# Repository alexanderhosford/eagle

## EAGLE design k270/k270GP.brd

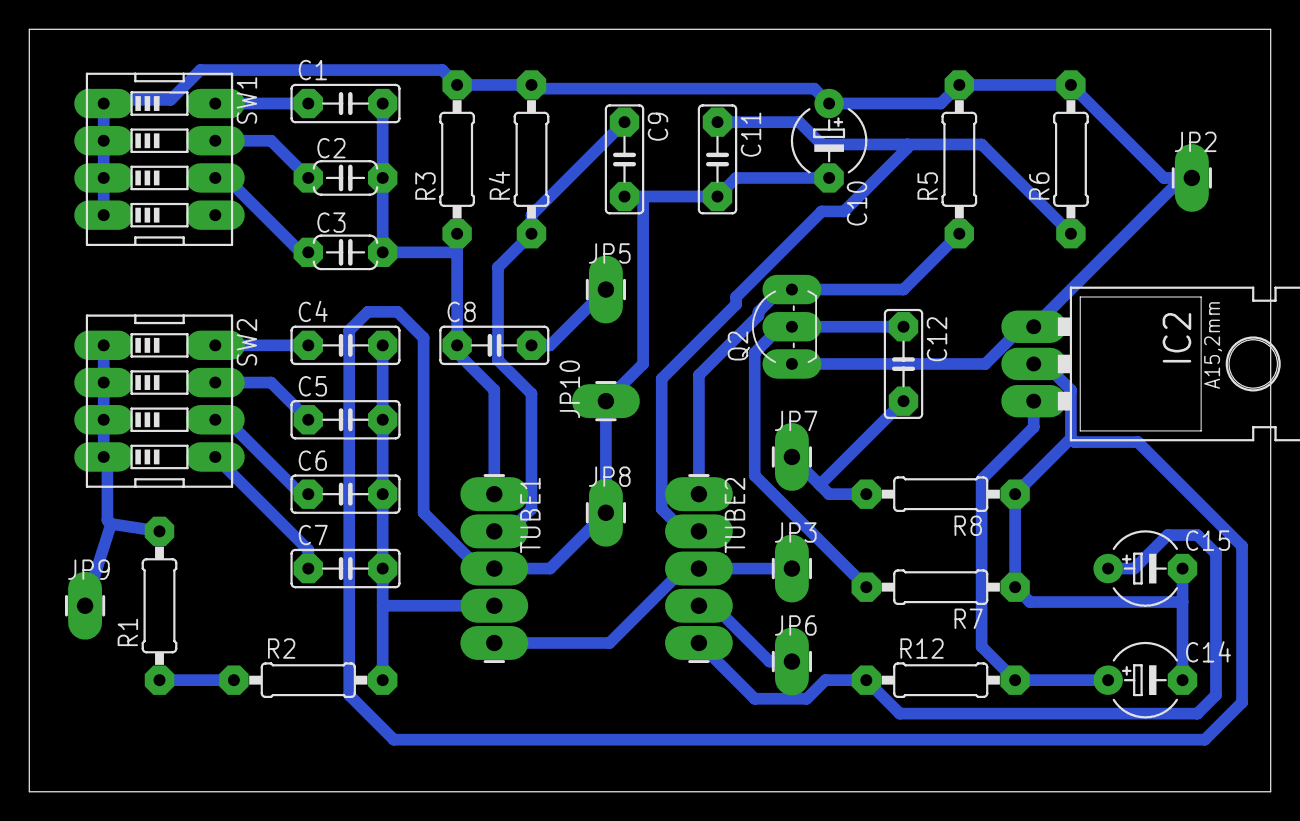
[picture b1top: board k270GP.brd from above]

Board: 2 copper layers, 84.8 x 52.1 mm, 37 parts (0 on the bottom side), 23 nets.

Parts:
C1, C6: 3n3; C050-025X075
C2: 820p; C050-024X044
C3: 330p; C050-024X044
C4: 100nF; C050-025X075
C5, C8: 10nF; C050-025X075
C7: 1n2; C050-025X075
C9, C11, C12: 0.1; C050-025X075
C10, C14, C15: 10µF; E5-5
IC2: 78XXL
JP2: +9V; 1X01_LONGPAD
JP3: pot1; 1X01_LONGPAD
JP5: pot3; 1X01_LONGPAD
JP6: potWiper; 1X01_LONGPAD
JP7: OUT.SIG; 1X01_LONGPAD
JP8: OUT.GND; 1X01_LONGPAD
JP9: IN.SIG; 1X01_LONGPAD
JP10: IN.GND; 1X01_LONGPAD
Q2: BSN254A; TO92-
R1, R8: 1M; 0207/10
R2: 47k; 0207/10
R3: 100k; 0207/10
R4, R6: 270k; 0207/10
R5: 180k; 0207/10
R7: 6k8; 0207/10
R12: 270R; 0207/10
SW1: LPF; EDG-04
SW2: HPF; EDG-04
TUBE1, TUBE2: JAN6841; 1X05_LONGPADS

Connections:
5V: C14.+, IC2.OUT, R12.2
9V: C10.+, IC2.IN, JP2.1, Q2.3, R3.2, R4.2, R5.2, R6.2, SW1.1, SW1.2, SW1.3, SW1.4
GND: C9.2, C10.-, C11.2, C14.-, C15.-, IC2.GND, JP8.1, JP10.1, R7.1, R8.1, TUBE1.3
unnamed: C1.1, SW1.8
unnamed: C2.1, SW1.7
unnamed: C3.1, SW1.6
unnamed: C1.2, C2.2, C3.2, C8.1, R3.1, TUBE1.1
unnamed: C4.1, SW2.8
unnamed: C5.1, SW2.7
unnamed: C6.1, SW2.6
unnamed: C7.1, SW2.5
unnamed: C4.2, C5.2, C6.2, C7.2, R2.2, TUBE1.4
unnamed: JP9.1, R1.2, SW2.1, SW2.2, SW2.3, SW2.4
unnamed: R1.1, R2.1
unnamed: C8.2, JP5.1
unnamed: C9.1, R4.1, TUBE1.2
unnamed: JP6.1, TUBE2.4
unnamed: C11.1, R6.1, TUBE2.2
unnamed: JP3.1, TUBE1.5, TUBE2.3
unnamed: C15.+, R12.1, TUBE2.5
unnamed: Q2.1, R5.1, TUBE2.1
unnamed: C12.1, Q2.2, R7.2
unnamed: C12.2, JP7.1, R8.2

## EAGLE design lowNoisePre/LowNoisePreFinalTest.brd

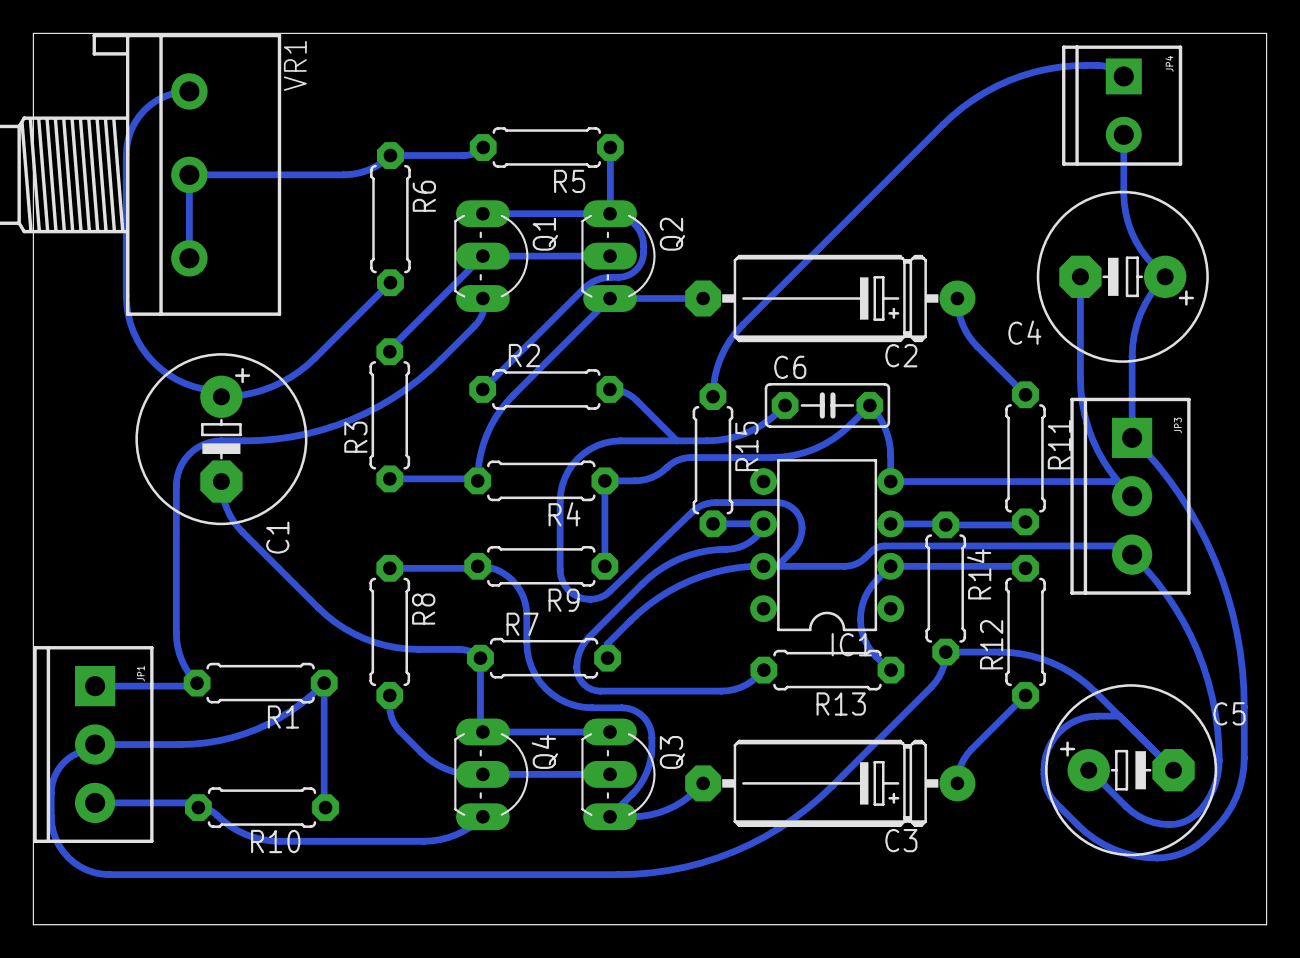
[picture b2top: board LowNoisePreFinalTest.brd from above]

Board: 2 copper layers, 73.9 x 53.4 mm, 30 parts (0 on the bottom side), 19 nets.

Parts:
C1: 1000µF; E5-10,5
C2, C3: 10µF; E15-5
C4, C5: 220µF; E5-10,5
C6: 100nF; C050-025X075
IC1: TL071P; DIL08
JP1: INPUT; SCREWTERMINAL-3.5MM-3
JP3: POWER; SCREWTERMINAL-3.5MM-3
JP4: OUTPUT; SCREWTERMINAL-3.5MM-2
Q1, Q4: 2N4403; TO92-BCE
Q2, Q3: BC549B; TO92-EBC
R1, R10: 3k3; 0207/7
R2, R7: 4k7; 0207/7
R3, R8: 680r; 0207/7
R4, R9: 2k2; 0207/7
R5: 22r; 0207/7
R6, R13, R14: 100k; 0207/7
R11, R12: 22k; 0207/7
R15: 100r; 0207/7
VR1: 10k; 3RP/1610N

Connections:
GND: C4.+, C5.-, JP1.2, JP3.1, JP4.2, R1.1, R10.1, R14.2
unnamed: C5.+, C6.1, IC1.7, JP3.3, R2.2, R7.2
unnamed: C4.-, C6.2, IC1.4, JP3.2, R4.1, R9.1
unnamed: JP4.1, R15.1
unnamed: IC1.6, R13.2, R15.2
unnamed: IC1.2, R12.2, R13.1
unnamed: IC1.3, R11.2, R14.1
unnamed: C3.+, R12.1
unnamed: C2.+, R11.1
unnamed: C3.-, Q3.E, R8.1, R9.2
unnamed: Q1.C, Q2.B, R3.2
unnamed: C2.-, Q2.E, R3.1, R4.2
unnamed: Q3.B, Q4.C, R8.2
unnamed: JP1.3, Q4.B, R10.2
unnamed: JP1.1, Q1.B, R1.2
unnamed: Q1.E, Q2.C, R2.1, R5.1
unnamed: C1.-, Q3.C, Q4.E, R7.1
unnamed: R5.2, R6.1, VR1.2, VR1.3
unnamed: C1.+, R6.2, VR1.1

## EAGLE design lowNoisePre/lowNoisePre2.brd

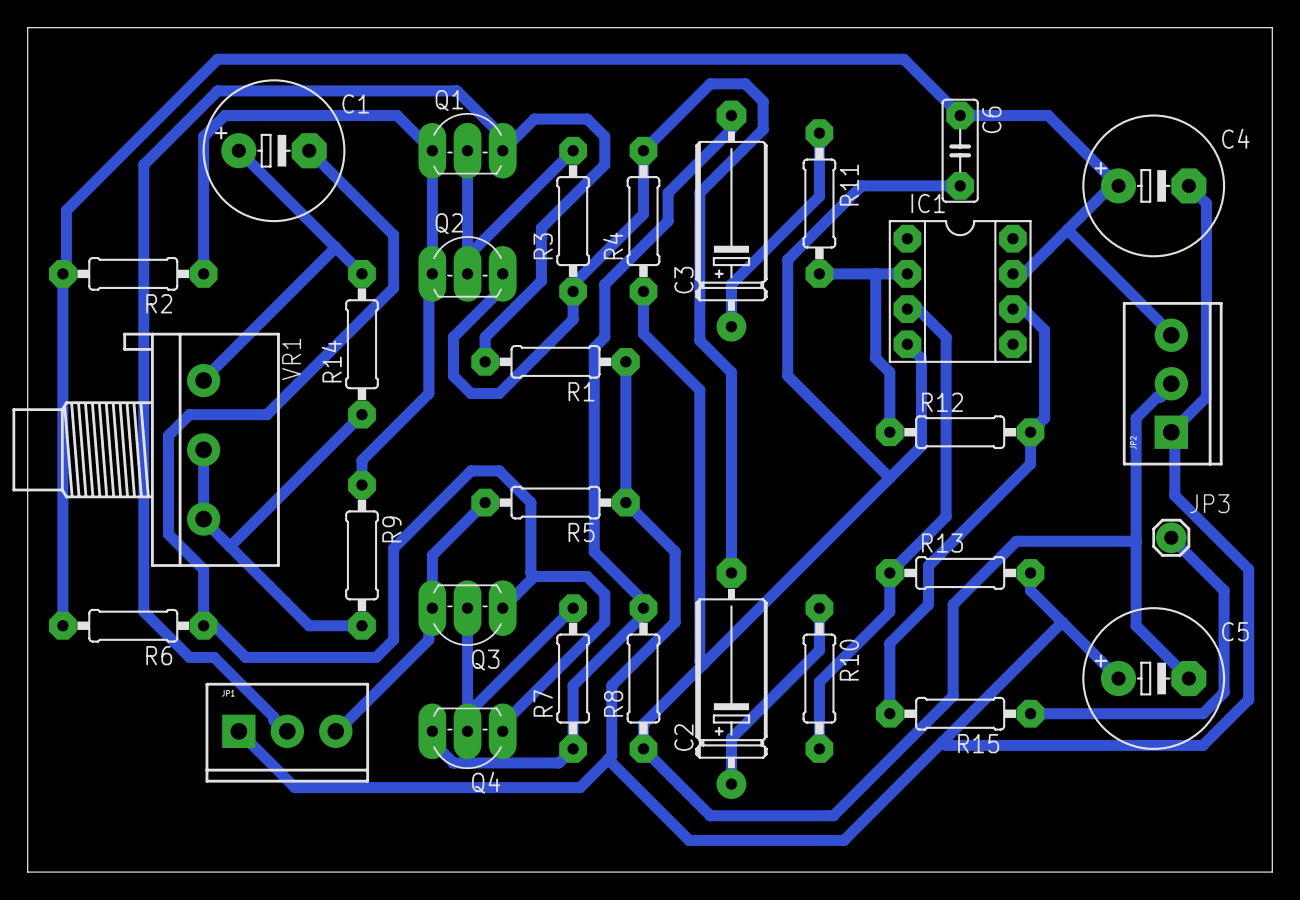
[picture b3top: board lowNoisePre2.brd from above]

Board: 2 copper layers, 89.8 x 60.9 mm, 30 parts (0 on the bottom side), 19 nets.

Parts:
C1: 1000µF; E5-10,5
C2, C3: 10µF; E15-5
C4, C5: 220µF; E5-10,5
C6: 100nF; C050-025X075
IC1: INA217P; DIL08
JP1: SCREWTERMINAL-3.5MM-3
JP2: POWER; SCREWTERMINAL-3.5MM-3
JP3: OUTPUT; 1X01
Q1: 2N4403; TO92-BCE
Q2, Q4: BC549B; TO92-EBC
Q3: BC369; TO92-BCE
R1, R5: 3k3; 0207/10
R2, R6: 4k7; 0207/10
R3, R7: 680r; 0207/10
R4, R8: 2k2; 0207/10
R9: 22r; 0207/10
R10, R11: 22k; 0207/10
R12, R13, R14: 100k; 0207/10
R15: 100r; 0207/10
VR1: 10k; 3RP/1610N

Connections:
GND: C4.-, C5.+, JP1.1, JP2.1, R1.1, R5.1, R13.2
unnamed: C4.+, C6.1, IC1.7, JP2.3, R2.2, R6.2
unnamed: C5.-, C6.2, IC1.4, JP2.2, R4.1, R8.1
unnamed: JP3.1, R15.1
unnamed: IC1.6, R12.2, R15.2
unnamed: IC1.2, R11.2, R12.1
unnamed: IC1.3, R10.2, R13.1
unnamed: C3.+, R11.1
unnamed: C2.+, R10.1
unnamed: C3.-, Q4.E, R7.1, R8.2
unnamed: Q1.C, Q2.B, R3.2
unnamed: C2.-, Q2.E, R3.1, R4.2
unnamed: Q3.C, Q4.B, R7.2
unnamed: JP1.3, Q3.B, R5.2
unnamed: JP1.2, Q1.B, R1.2
unnamed: Q1.E, Q2.C, R2.1, R9.1
unnamed: C1.-, Q3.E, Q4.C, R6.1
unnamed: R9.2, R14.1, VR1.2, VR1.3
unnamed: C1.+, R14.2, VR1.1

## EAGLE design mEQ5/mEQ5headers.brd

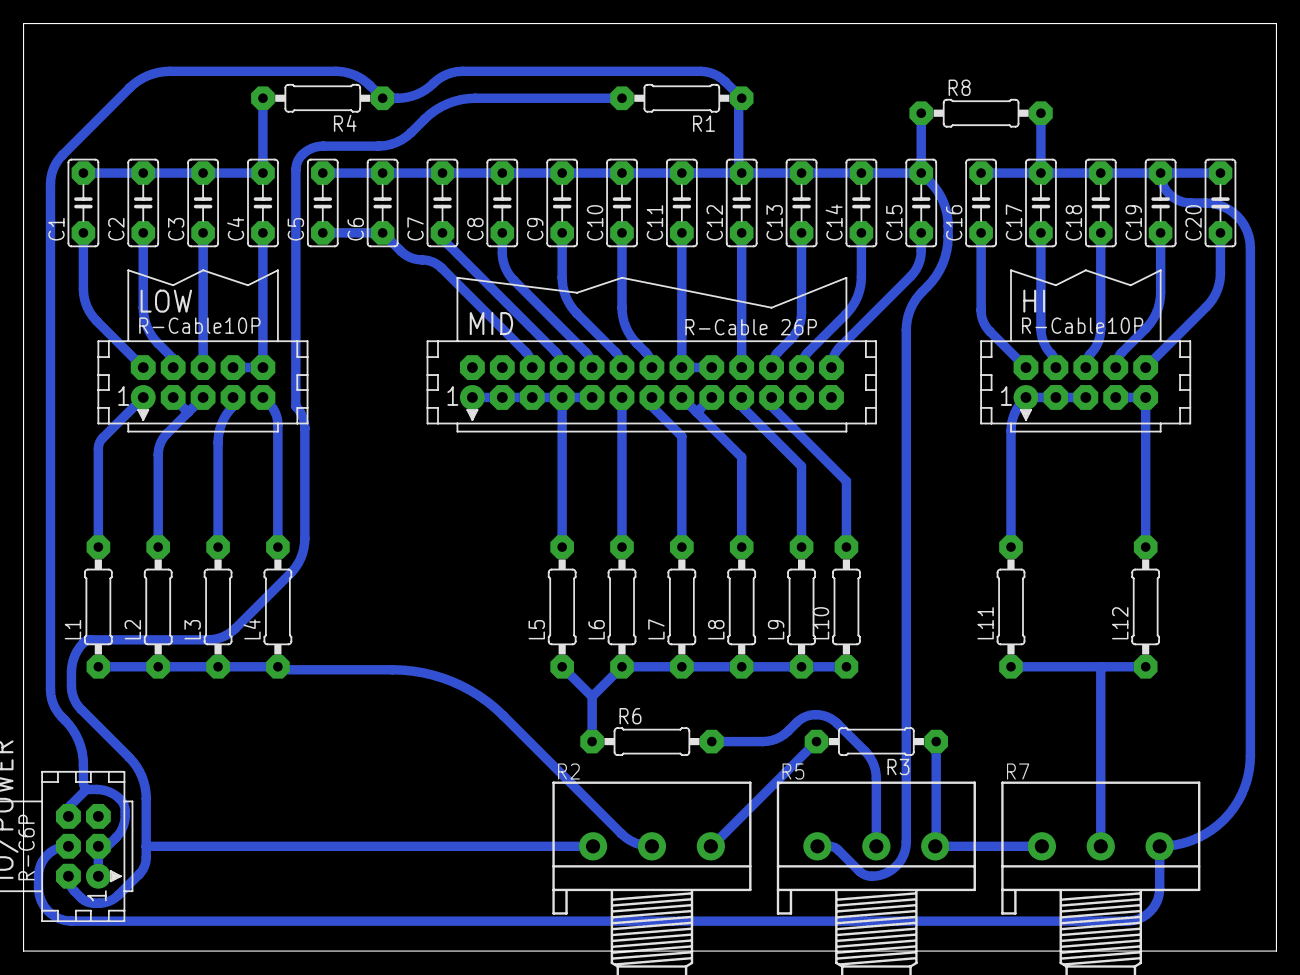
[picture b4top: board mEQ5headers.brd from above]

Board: 2 copper layers, 106.4 x 78.7 mm, 44 parts (0 on the bottom side), 41 nets.

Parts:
C1, C7: 1µ; C050-025X075
C2: 470n; C050-025X075
C3: 150n; C050-025X075
C4: 200n; C050-025X075
C5: 1µ5; C050-025X075
C6: 15n; C050-025X075
C8: 600n; C050-025X075
C9: 330n; C050-025X075
C10: 220n; C050-025X075
C11: 170n; C050-025X075
C12: 68n; C050-025X075
C13: 30n; C050-025X075
C14, C16: 16n; C050-025X075
C15: 10n; C050-025X075
C17: 8n2; C050-025X075
C18: 3n9; C050-025X075
C19: 2n; C050-025X075
C20: 1n; C050-025X075
HI: CON10
IO/POWER: CON06
L1: 120µH; 0207/10
L2: 280µH; 0207/10
L3, L10: 420µH; 0207/10
L4: 520µH; 0207/10
L5: 34µH; 0207/10
L6: 61µH; 0207/10
L7: 108µH; 0207/10
L8: 145µH; 0207/10
L9: 277µH; 0207/10
L11: 477µH; 0207/10
L12: 625µH; 0207/10
LOW: CON10
MID: CON26
R1: 620R; 0207/10
R2: 2k5A; 3RP/1610N
R3: 510R; 0207/10
R4: 1k; 0207/10
R5: 2k5C; 3RP/1610N
R6: 270R; 0207/10
R7: 10kA; 3RP/1610N
R8: 5k1; 0207/10

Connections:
GND: C5.2, C6.2, C7.2, C8.2, C9.2, C10.2, C11.2, C12.2, C13.2, C14.2, C15.2, IO/POWER.1, IO/POWER.3, IO/POWER.6, R1.1, R4.1, R5.1, R8.1
unnamed: L1.2, LOW.1
unnamed: L2.2, LOW.3, LOW.5
unnamed: L3.2, LOW.7
unnamed: L4.2, LOW.9
unnamed: C4.1, LOW.8, LOW.10
unnamed: C3.1, LOW.6
unnamed: C2.1, LOW.4
unnamed: C1.1, LOW.2
unnamed: L5.2, MID.1, MID.3, MID.5, MID.7, MID.9
unnamed: L6.2, MID.11
unnamed: L7.2, MID.13
unnamed: L8.2, MID.15, MID.17
unnamed: L9.2, MID.19
unnamed: L10.2, MID.21
unnamed: C7.1, MID.8
unnamed: C8.1, MID.10
unnamed: C9.1, MID.12
unnamed: C10.1, MID.14
unnamed: C11.1, MID.16, MID.18
unnamed: C12.1, MID.20
unnamed: C13.1, MID.22
unnamed: C14.1, MID.24
unnamed: C5.1, C6.1, MID.6
unnamed: C15.1, MID.26
unnamed: HI.1, HI.3, HI.5, L11.2
unnamed: HI.7, HI.9, L12.2
unnamed: C16.1, HI.2
unnamed: C20.1, HI.10
unnamed: C19.1, HI.8
unnamed: C17.1, HI.4
unnamed: L1.1, L2.1, L3.1, L4.1, R2.2
unnamed: IO/POWER.2, R1.2, R2.1
unnamed: C1.2, C2.2, C3.2, C4.2, R4.2
unnamed: R2.3, R3.2
unnamed: R3.1, R5.3, R7.1
unnamed: R5.2, R6.2
unnamed: L5.1, L6.1, L7.1, L8.1, L9.1, L10.1, R6.1
unnamed: L11.1, L12.1, R7.2
unnamed: C18.1, HI.6
unnamed: C16.2, C17.2, C18.2, C19.2, C20.2, IO/POWER.4, R7.3, R8.2

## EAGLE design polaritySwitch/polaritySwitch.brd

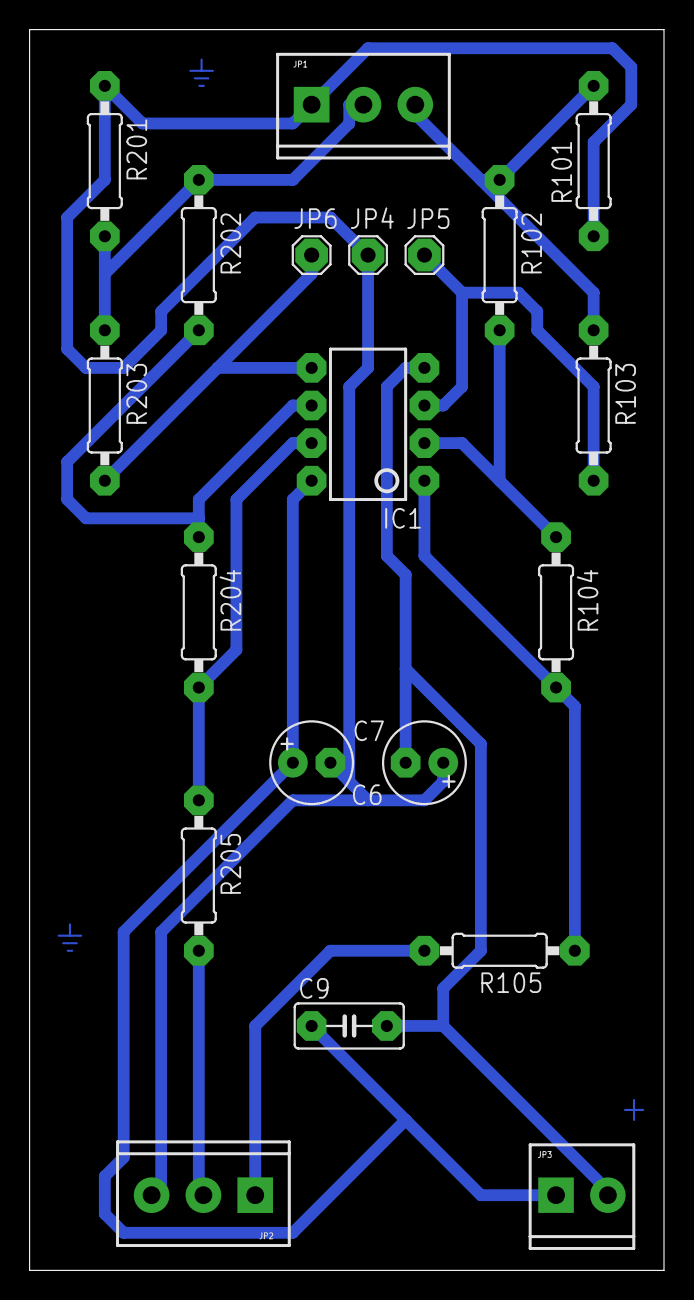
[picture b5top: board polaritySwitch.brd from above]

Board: 2 copper layers, 42.9 x 83.8 mm, 20 parts (0 on the bottom side), 13 nets.

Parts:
C6, C7: 10µF; E2,5-6
C9: 100nF; C050-030X075
IC1: TL072; DIP08
JP1: INPUT; SCREWTERMINAL-3.5MM-3
JP2: OUTPUT; SCREWTERMINAL-3.5MM-3
JP3: VE; SCREWTERMINAL-3.5MM-2
JP4, JP5, JP6: 1X01
R101, R201: 100K; 0207/10
R102, R103, R104, R202, R203, R204: 22K; 0207/10
R105, R205: 100R; 0207/10

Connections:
unnamed: C7.+, C9.1, IC1.8, JP3.1
unnamed: IC1.1, R104.2, R105.1
unnamed: IC1.5, JP6.1, R203.2
unnamed: JP1.2, R201.2, R202.1, R203.1
unnamed: IC1.3, JP5.1, R103.2
unnamed: IC1.7, R204.2, R205.1
unnamed: IC1.6, R202.2, R204.1
unnamed: C6.-, C9.2, IC1.4, JP3.2
unnamed: C6.+, C7.-, JP1.1, JP2.3, JP4.1, R101.1, R201.1
unnamed: JP1.3, R101.2, R102.1, R103.1
unnamed: IC1.2, R102.2, R104.1
unnamed: JP2.2, R205.2
unnamed: JP2.1, R105.2

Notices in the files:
parts and their libraries:
SparkFun: Licensing: CC v3.0 Share-Alike You are welcome to use this library for commercial purposes.
